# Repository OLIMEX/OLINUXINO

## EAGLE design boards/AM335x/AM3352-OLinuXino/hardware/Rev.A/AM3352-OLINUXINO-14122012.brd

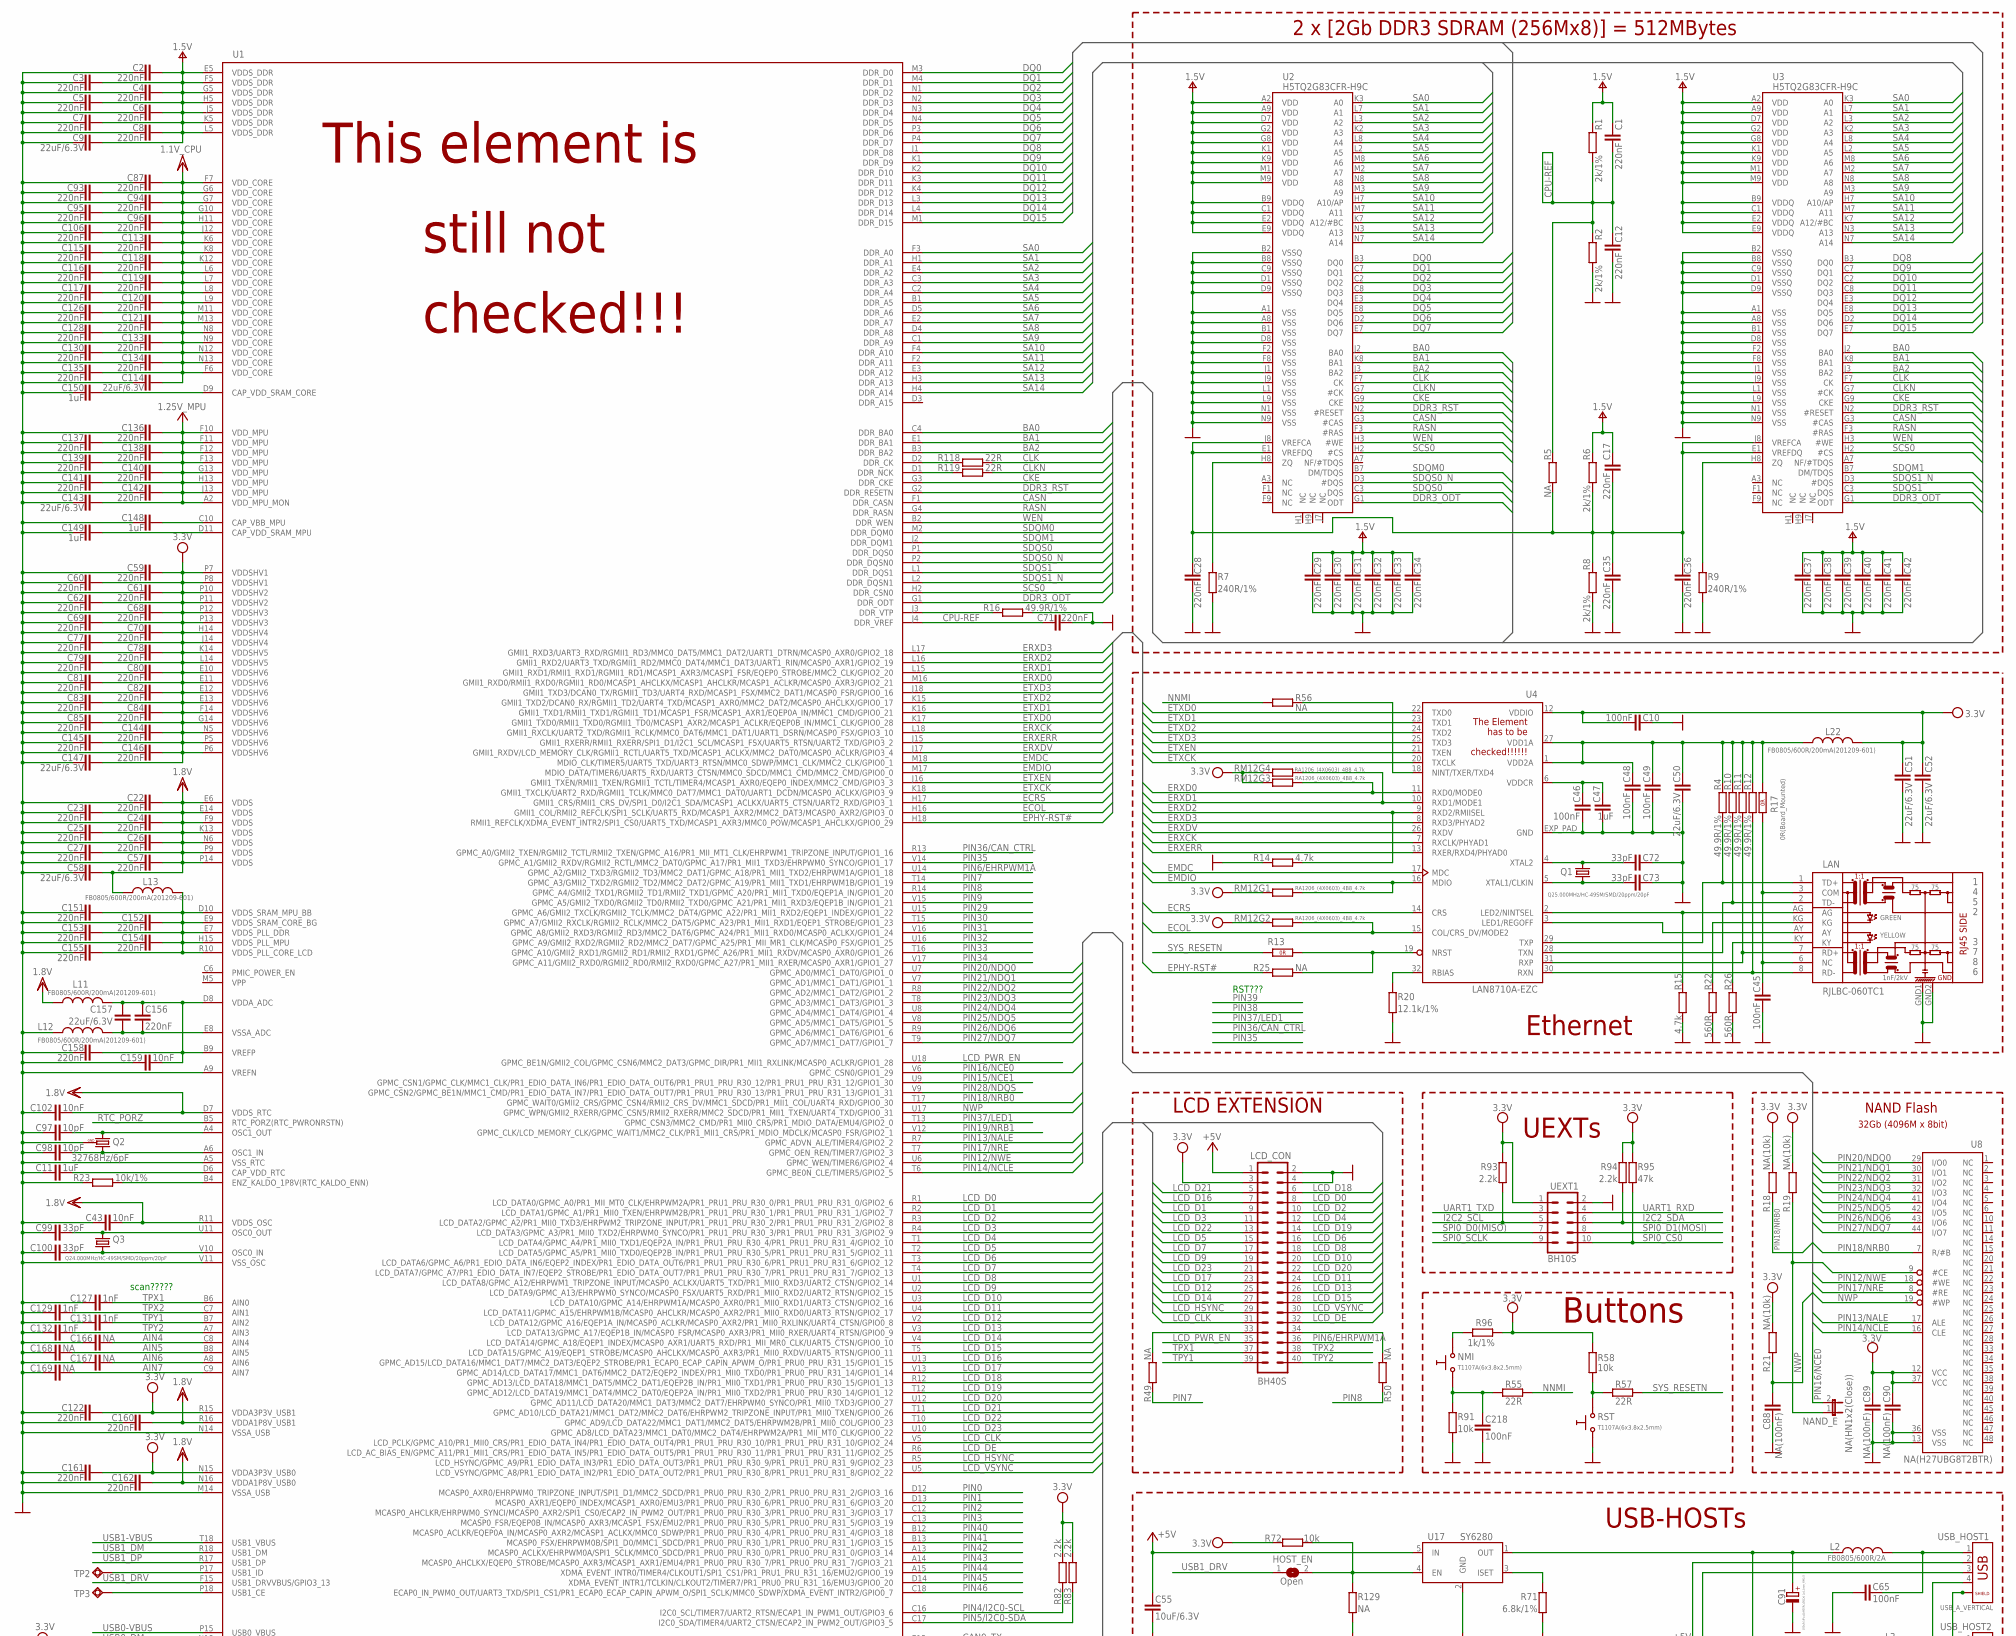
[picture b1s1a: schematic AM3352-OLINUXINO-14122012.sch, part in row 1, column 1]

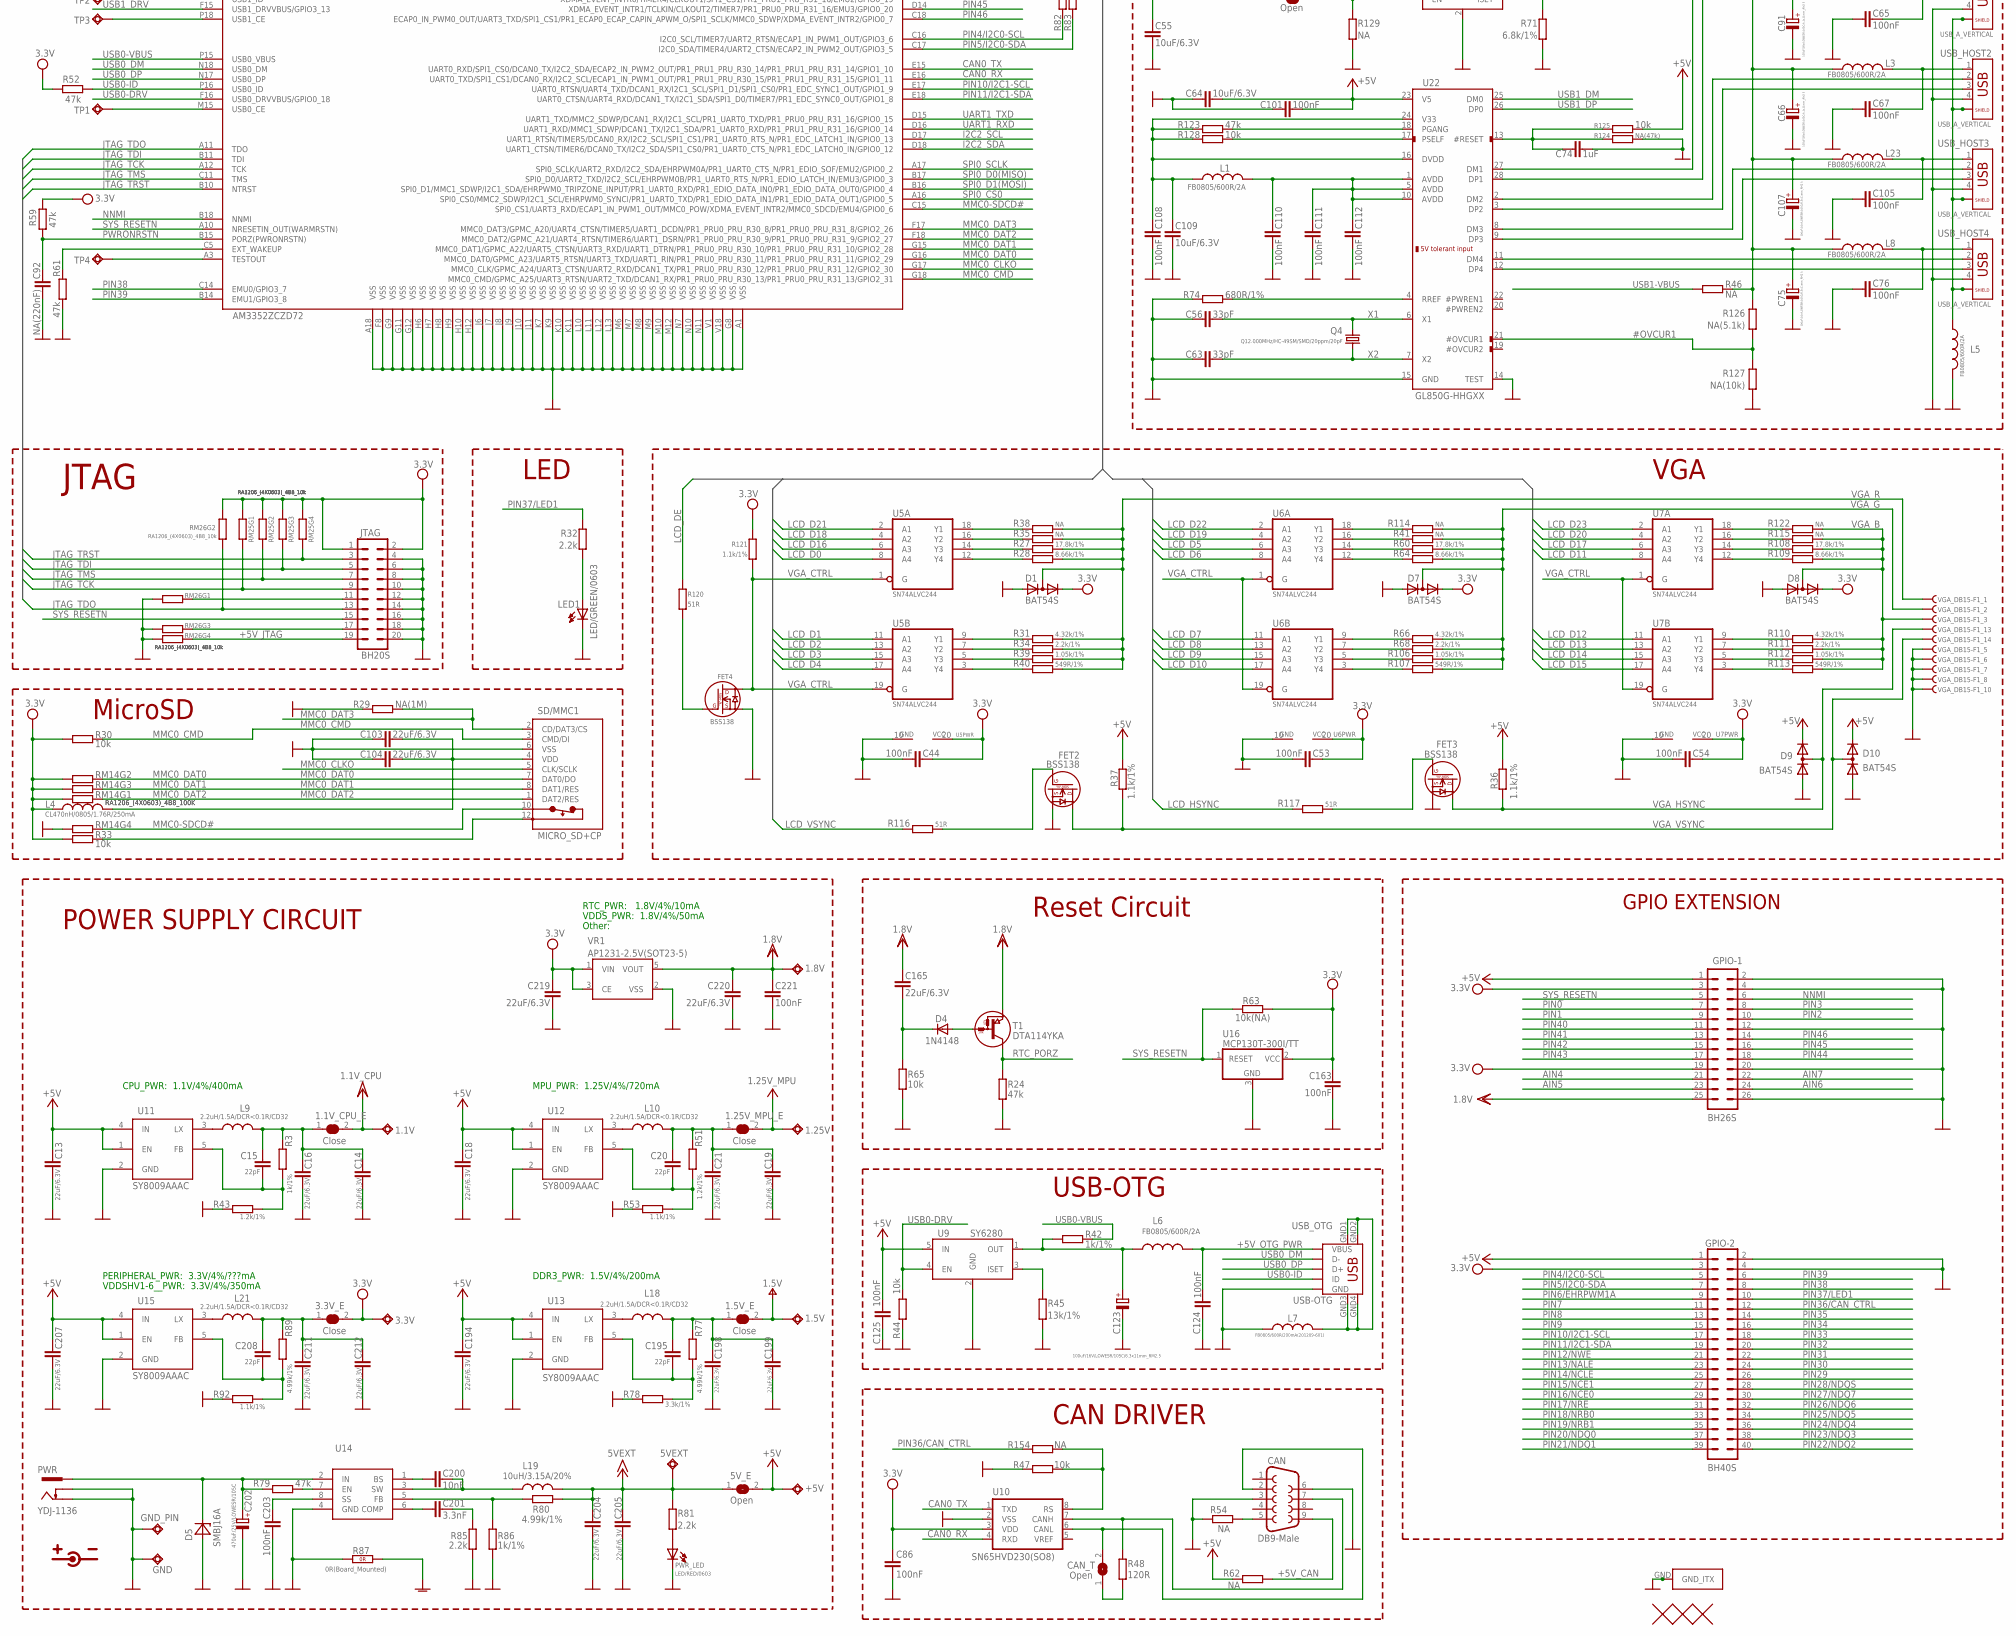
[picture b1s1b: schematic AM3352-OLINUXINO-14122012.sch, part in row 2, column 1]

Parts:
1.1V, 1.5V, 1.8V, 1.25V, 3.3V, 5VEXT: TESTPADTESTPAD_40-ROUND; TESTPAD_40-ROUND
1.1V_CPU_E, 1.5V_E, 1.25V_MPU_E, 3.3V_E: Close; SJ_1_SMALLER_CLOSE
5V_E: Open; SJ_1_SMALLER
+5V: TESTPADTESTPAD_40-ROUND; TESTPAD_40-ROUND
C1, C2, C3, C4, C5, C6, C7, C8, C12, C17, C22, C23, C24, C25, C26, C27, C28, C29, C30, C31, C32, C33, C34, C35, C36, C37, C38, C39, C40, C41, C42, C57, C59, C60, C61, C62, C68, C69, C70, C71, C77, C78, C79, C80, C81, C82, C83, C84, C85, C87, C93, C94, C95, C96, C106, C113, C115, C116, C117, C118, C119, C120, C121, C122, C126, C128, C130, C133, C134, C135, C136, C137, C138, C139, C140, C141, C142, C144, C145, C146, C151, C152, C153, C154, C155, C156, C158, C160, C161, C162: 220nF; C0603_DWS
C9, C13, C14, C16, C18, C19, C21, C50, C51, C52, C58, C103, C104, C114, C143, C147, C157, C165, C194, C198, C199, C204, C205, C207, C211, C212, C219, C220: 22uF/6.3V; C0603_DWS
C10, C44, C45, C46, C48, C49, C53, C54, C65, C67, C76, C86, C101, C105, C108, C110, C111, C112, C124, C125, C163, C203, C218, C221: 100nF; C0603_DWS
C11, C47, C74, C148, C149, C150: 1uF; C0603_DWS
C15, C20, C195, C208: 22pF; C0603_DWS
C43, C102, C159, C200: 10nF; C0603_DWS
C55, C64, C109: 10uF/6.3V; C0603_DWS
C56, C63, C72, C73, C99, C100: 33pF; C0603_DWS
C66, C75, C91, C107, C123: 100uF/16V/LOWESR/105C/6.3x11mm_RM2.5; E2,5-6,3
C88, C89, C90: NA(100nF); C0603_DWS
C92: NA(220nF); C0603_DWS
C97, C98: 10pF; C0603_DWS
C127, C129, C131, C132: 1nF; C0603_DWS
C166, C167, C168, C169: NA; C0603_DWS
C201: 3.3nF; C0603_DWS
C202: 470uF/25V/LOWESR/105C; E5-10,5
CAN: DB9-Male; F09HP-MALE
CAN_T: Open; SJ
D1, D7, D8, D9, D10: BAT54S; SOT23C(BAT54S)
D4: 1N4148; MELF-MLL41
D5: SMBJ16A; DO214AA
FET2, FET3, FET4: BSS138; SOT23
GND: TESTPADTESTPAD_40-ROUND; TESTPAD_40-ROUND
GND_PIN: TESTPAD3; TEST_PAD40/70/SQUARE
GPIO-1: BH26S; ML26
GPIO-2: BH40S; ML40
HOST_EN: Open; SJ_1_SMALLER
JTAG: BH20S; ML20-MALE
L1, L2, L3, L5, L6, L8, L23: FB0805/600R/2A; L0805_5MIL_DWS
L4: CL470nH/0805/1.76R/250mA; L0805_5MIL_DWS
L7, L11, L12, L13, L22: FB0805/600R/200mA(201209-601); L0805_5MIL_DWS
L9, L10, L18, L21: 2.2uH/1.5A/DCR<0.1R/CD32; CD32
L19: 10uH/3.15A/20%; 8X8MM_3131
LAN: RJLBC-060TC1
LCD_CON: BH40S; ML40
LED1: LED/GREEN/0603; LED-0603
NAND_E: NA(HN1x2(Close)); JP1
NMI: T1107A(6x3.8x2.5mm); SW-TAKT_6X3.5_SMD
PWR: YDJ-1136; PWR_JACK_UNI_MILLING
PWR_LED: LED/RED/0603; LED-0603
Q1: Q25.000MHz/HC-49SM/SMD/20ppm/20pF; HC49/SMD2_THIN
Q2: 32768Hz/6pF; TC26H_3_REPAIR_SMD
Q3: Q24.000MHz/HC-49SM/SMD/20ppm/20pF; HC49/SMD2_THIN
Q4: Q12.000MHz/HC-49SM/SMD/20ppm/20pF; HC49/SMD2_THIN
R1, R2, R6, R8: 2k/1%; R0603_5MIL_DWS
R3, R42, R86, R96: 1k/1%; R0603_5MIL_DWS
R4, R10, R11, R12, R16: 49.9R/1%; R0603_5MIL_DWS
R5, R25, R35, R38, R41, R46, R49, R50, R56, R114, R115, R122, R129: NA; R0603_5MIL_DWS
R7, R9: 240R/1%; R0603_5MIL_DWS
R13: R_0R0R(NA); 0603_0R
R14, R15: 4.7k; R0603_5MIL_DWS
R17, R87: 0R(Board_Mounted); 0603_0R
R18, R19, R21, R127: NA(10k); R0603_5MIL_DWS
R20: 12.1k/1%; R0603_5MIL_DWS
R22, R26: 560R; R0603_5MIL_DWS
R23: 10k/1%; R0603_5MIL_DWS
R24, R52, R59, R61, R79, R95, R123: 47k; R0603_5MIL_DWS
R27, R60, R108: 17.8k/1%; R0603_5MIL_DWS
R28, R64, R109: 8.66k/1%; R0603_5MIL_DWS
R29: NA(1M); R0603_5MIL_DWS
R30, R33, R44, R47, R58, R65, R72, R91, R125, R128: 10k; R0603_5MIL_DWS
R31, R66, R110: 4.32k/1%; R0603_5MIL_DWS
R32, R81, R82, R83, R85, R93, R94: 2.2k; R0603_5MIL_DWS
R34, R68, R111: 2.2k/1%; R0603_5MIL_DWS
R36, R37, R53, R92, R121: 1.1k/1%; R0603_5MIL_DWS
R39, R106, R112: 1.05k/1%; R0603_5MIL_DWS
R40, R107, R113: 549R/1%; R0603_5MIL_DWS
R43, R51: 1.2k/1%; R0603_5MIL_DWS
R45: 13k/1%; R0603_5MIL_DWS
R48: 120R; R1206_5MIL_WS
R54, R62, R154: NA; R0603_5MIL_DWS_NA
R55, R57, R118, R119: 22R; R0603_5MIL_DWS
R63: 10k(NA); R0603_5MIL_DWS
R71: 6.8k/1%; R0603_5MIL_DWS
R74: 680R/1%; R0603_5MIL_DWS
R77, R80, R89: 4.99k/1%; R0603_5MIL_DWS
R78: 3.3k/1%; R0603_5MIL_DWS
R116, R117, R120: 51R; R0603_5MIL_DWS
R124: NA(47k); R0603_5MIL_DWS
R126: NA(5.1k); R0603_5MIL_DWS
RM12: RA1206_(4X0603)_4B8_4.7k; R_MATRIX_4
RM14: RA1206_(4X0603)_4B8_100K; R_MATRIX_4
RM25, RM26: RA1206_(4X0603)_4B8_10k; R_MATRIX_4
RST: T1107A(6x3.8x2.5mm); SW-TAKT_6X3.5_SMD
SD/MMC1: MICRO_SD+CP; TFR-MEM-CON
T1: DTA114YKA; SOT-23
TP1, TP2, TP3, TP4: TESTPADTESTPAD_40-ROUND; TESTPAD_40-ROUND
U1: AM3352ZCZD72; S-PBGA-N324
U2, U3: H5TQ2G83CFR-H9C; FBGA78
U4: LAN8710A-EZC; QFN-32
U5, U6, U7: SN74ALVC244; PW
U8: NA(H27UBG8T2BTR); TSOP48
U9, U17: SY6280; SOT23-5
U10: SN65HVD230(SO8); SO-08
U11, U12, U13, U15: SY8009AAAC; SOT23-5
U14: MP1482DS; SOIC8
U16: MCP130T-300I/TT; SOT23
U19, U20, U21: FIDUCIAL1X2; FIDUCIAL-1X2
U22: GL850G-HHGXX; SSOP28
U$1: NANO_ITX_; NANO-ITX_140X140
UEXT1: BH10S; ML10-MALE
USB_HOST1, USB_HOST2, USB_HOST3, USB_HOST4: USB_A_VERTICAL; USB_A_VERTICAL_PTH
USB_OTG: USB-OTG; USB_MINI_9PIN
VGA_DB15-F1: VGA15; DB15-F_22MM
VR1: AP1231-2.5V(SOT23-5); SOT-23-5

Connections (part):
#OVCUR1: R126.1, R127.2, U22.21 (#OVCUR1)
+5V: 5V_E.2, +5V.1, C13.1, C18.1, C55.1, C64.1, C101.1, C125.1, C194.1, C207.1, D9.2 (K), D10.2 (K), GPIO-1.1, GPIO-2.1, LCD_CON.1, R36.2, R37.2, R62.1, R125.2, U9.5 (IN), U11.1 (EN), U11.4 (IN), U12.1 (EN), U12.4 (IN), U13.1 (EN), U13.4 (IN), U15.1 (EN), U15.4 (IN), U17.5 (IN), U22.23 (V5)
+5V_CAN: CAN.9, R62.2
+5V_JTAG: JTAG.19, RM26.4.2 (2)
+5V_OTG_PWR: C124.1, L6.1, USB_OTG.VBUS
+15V: 5VEXT.1, 5V_E.1, C204.1, C205.1, L19.2, R80.2, R81.1
AIN4: C166.2, GPIO-1.21, U1.C8 (AIN4)
AIN5: C168.2, GPIO-1.23, U1.B8 (AIN5)
AIN6: C167.2, GPIO-1.24, U1.A8 (AIN6)
AIN7: C169.2, GPIO-1.22, U1.C9 (AIN7)
AVDD1: C110.1, C111.1, C112.1, L1.2, U22.1 (AVDD), U22.5 (AVDD), U22.10 (AVDD)
BA0: U1.C4 (DDR_BA0), U2.J2 (BA0), U3.J2 (BA0)
BA1: U1.E1 (DDR_BA1), U2.K8 (BA1), U3.K8 (BA1)
BA2: U1.B3 (DDR_BA2), U2.J3 (BA2), U3.J3 (BA2)
CAN0_RX: U1.E16 (UART0_TXD/SPI1_CS1/DCAN0_RX/I2C2_SCL/EC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), U10.4 (RXD)
CAN0_TX: U1.E15 (UART0_RXD/SPI1_CS0/DCAN0_TX/I2C2_SDA/EC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), U10.1 (TXD)
CANH: CAN.7, R48.2, U10.7 (CANH)
CANL: CAN.2, CAN_T.2, U10.6 (CANL)
CASN: U1.F1 (DDR_CASN), U2.G3 (#CAS), U3.G3 (#CAS)
CKE: U1.G3 (DDR_CKE), U2.G9 (CKE), U3.G9 (CKE)
CLK: R118.1, U2.F7 (CK), U3.F7 (CK)
CLKN: R119.1, U2.G7 (#CK), U3.G7 (#CK)
CPU-REF: C1.2, C12.2, C71.2, R1.1, R2.2, R5.2, U1.J4 (DDR_VREF)
DDR3_ODT: U1.G1 (DDR_ODT), U2.G1 (ODT), U3.G1 (ODT)
DDR3_RST: U1.G2 (DDR_RESETN), U2.N2 (#RESET), U3.N2 (#RESET)
DM1: U22.27 (DM1), USB_HOST1.2
DM2: U22.2 (DM2), USB_HOST2.2
DM3: U22.8 (DM3), USB_HOST3.2
DM4: U22.11 (DM4), USB_HOST4.2
DP1: U22.28 (DP1), USB_HOST1.3
DP2: U22.3 (DP2), USB_HOST2.3
DP3: U22.9 (DP3), USB_HOST3.3
DP4: U22.12 (DP4), USB_HOST4.3
DQ0: U1.M3 (DDR_D0), U2.B3 (DQ0)
DQ1: U1.M4 (DDR_D1), U2.C7 (DQ1)
DQ2: U1.N1 (DDR_D2), U2.C2 (DQ2)
DQ3: U1.N2 (DDR_D3), U2.C8 (DQ3)
DQ4: U1.N3 (DDR_D4), U2.E3 (DQ4)
DQ5: U1.N4 (DDR_D5), U2.E8 (DQ5)
DQ6: U1.P3 (DDR_D6), U2.D2 (DQ6)
DQ7: U1.P4 (DDR_D7), U2.E7 (DQ7)
DQ8: U1.J1 (DDR_D8), U3.B3 (DQ0)
DQ9: U1.K1 (DDR_D9), U3.C7 (DQ1)
DQ10: U1.K2 (DDR_D10), U3.C2 (DQ2)
DQ11: U1.K3 (DDR_D11), U3.C8 (DQ3)
DQ12: U1.K4 (DDR_D12), U3.E3 (DQ4)
DQ13: U1.L3 (DDR_D13), U3.E8 (DQ5)
DQ14: U1.L4 (DDR_D14), U3.D2 (DQ6)
DQ15: U1.M1 (DDR_D15), U3.E7 (DQ7)
DRAM-REF: C17.2, C28.2, C35.2, C36.2, R5.1, R6.1, R8.2, U2.E1 (VREFDQ), U2.J8 (VREFCA), U3.E1 (VREFDQ), U3.J8 (VREFCA)
DVDD1: C108.1, C109.1, L1.1, R123.1, R128.1, U22.16 (DVDD), U22.24 (V33)
ECOL: RM12.2.2 (2), U1.H16 (GMII1_COL/RMII2_REFCLK/SPI1_SCLK/UART5_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), U4.15 (COL/CRS_DV/MODE2)
ECRS: U1.H17 (GMII1_CRS/RMII1_CRS_DV/SPI1_D0/I2C1_SDA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), U4.14 (CRS)
EMDC: U1.M18 (MDIO_CLK/TIMER5/UART5_TXD/UART3_RTSN/MM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), U4.17 (MDC)
EMDIO: RM12.1.2 (2), U1.M17 (MDIO_DATA/TIMER6/UART5_RXD/UART3_CTSN/M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), U4.16 (MDIO)
EPHY-RST#: R25.1, U1.H18 (RMII1_REFCLK/XDMA_EVENT_INTR2/SPI1_CS0/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)
ERXCK: U1.L18 (GMII1_RXCLK/UART2_TXD/RGMII1_RCLK/MMC0_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), U4.7 (RXCLK/PHYAD1)
ERXD0: RM12.3.2 (2), U1.M16 (GMII1_RXD0/RMII1_RXD0/RGMII1_RD0/MCASP1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), U4.11 (RXD0/MODE0)
ERXD1: RM12.4.2 (2), U1.L15 (GMII1_RXD1/RMII1_RXD1/RGMII1_RD1/MCASP1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), U4.10 (RXD1/MODE1)
ERXD2: R14.2, U1.L16 (GMII1_RXD2/UART3_TXD/RGMII1_RD2/MMC0_DA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), U4.9 (RXD2/RMIISEL)
ERXD3: U1.L17 (GMII1_RXD3/UART3_RXD/RGMII1_RD3/MMC0_DA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), U4.8 (RXD3/PHYAD2)
ERXDV: U1.J17 (GMII1_RXDV/LCD_MEMORY_CLK/RGMII1_RCTL/U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), U4.26 (RXDV)
ERXERR: U1.J15 (GMII1_RXERR/RMII1_RXERR/SPI1_D1/I2C1_SC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), U4.13 (RXER/RXD4/PHYAD0)
ETXCK: U1.K18 (GMII1_TXCLK/UART2_RXD/RGMII1_TCLK/MMC0_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), U4.20 (TXCLK)
ETXD0: U1.K17 (GMII1_TXD0/RMII1_TXD0/RGMII1_TD0/MCASP1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), U4.22 (TXD0)
ETXD1: U1.K16 (GMII1_TXD1/RMII1_TXD1/RGMII1_TD1/MCASP1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), U4.23 (TXD1)
ETXD2: U1.K15 (GMII1_TXD2/DCAN0_RX/RGMII1_TD2/UART4_TX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), U4.24 (TXD2)
ETXD3: U1.J18 (GMII1_TXD3/DCAN0_TX/RGMII1_TD3/UART4_RX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), U4.25 (TXD3)
ETXEN: U1.J16 (GMII1_TXEN/RMII1_TXEN/RGMII1_TCTL/TIMER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), U4.21 (TXEN)
GND: C2.1, C3.1, C4.1, C5.1, C6.1, C7.1, C8.1, C9.1, C10.1, C11.1, C12.1, C13.2, C14.2, C16.2, C18.2, C19.2, C21.2, C22.1, C23.1, C24.1, C25.1, C26.1, C27.1, C28.1, C29.1, C30.1, C31.1, C32.1, C33.1, C34.1, C35.1, C36.1, C37.1, C38.1, C39.1, C40.1, C41.1, C42.1, C43.1, C44.2, C45.1, C46.1, C47.1, C48.1, C49.1, C50.1, C51.1, C52.1, C53.2, C54.2, C55.2, C56.1, C57.1, C58.1, C59.1, C60.1, C61.1, C62.1, C63.1, C64.2, C65.2, C66.-, C67.2, C68.1, C69.1, C70.1, C71.1, C72.1, C73.1, C74.1, C75.-, C76.2, C77.1, C78.1, C79.1, C80.1, C81.1, C82.1, C83.1, C84.1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
GNDA: R87.2 (1.2)
I2C2_SCL: R93.1, U1.D17 (UART1_RTSN/TIMER5/DCAN0_RX/I2C2_SCL/SPI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), UEXT1.5
I2C2_SDA: R94.1, U1.D18 (UART1_CTSN/TIMER6/DCAN0_TX/I2C2_SDA/SPI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), UEXT1.6
JTAG_TCK: JTAG.9, RM25.1.1 (1), U1.A12 (TCK)
JTAG_TDI: JTAG.5, RM25.3.1 (1), U1.B11 (TDI)
JTAG_TDO: JTAG.13, RM26.2.2 (2), U1.A11 (TDO)
JTAG_TMS: JTAG.7, RM25.2.1 (1), U1.C11 (TMS)
JTAG_TRST: JTAG.3, RM25.4.1 (1), U1.B10 (NTRST)
LCD_CLK: LCD_CON.31, U1.V5 (LCD_PCLK/GPMC_A10/PR1_MII0_CRS/PR1_EDIO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)
LCD_D0: LCD_CON.8, U1.R1 (LCD_DATA0/GPMC_A0/PR1_MII_MT0_CLK/EHRPW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), U5.8 (A4)
LCD_D1: LCD_CON.9, U1.R2 (LCD_DATA1/GPMC_A1/PR1_MII0_TXEN/EHRPWM2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), U5.11 (A1)
LCD_D2: LCD_CON.10, U1.R3 (LCD_DATA2/GPMC_A2/PR1_MII0_TXD3/EHRPWM2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), U5.13 (A2)
LCD_D3: LCD_CON.11, U1.R4 (LCD_DATA3/GPMC_A3/PR1_MII0_TXD2/EHRPWM0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), U5.15 (A3)
LCD_D4: LCD_CON.12, U1.T1 (LCD_DATA4/GPMC_A4/PR1_MII0_TXD1/EQEP2A_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), U5.17 (A4)
LCD_D5: LCD_CON.15, U1.T2 (LCD_DATA5/GPMC_A5/PR1_MII0_TXD0/EQEP2B_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), U6.6 (A3)
LCD_D6: LCD_CON.16, U1.T3 (LCD_DATA6/GPMC_A6/PR1_EDIO_DATA_IN6/EQE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), U6.8 (A4)
LCD_D7: LCD_CON.17, U1.T4 (LCD_DATA7/GPMC_A7/PR1_EDIO_DATA_IN7/EQE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), U6.11 (A1)
LCD_D8: LCD_CON.18, U1.U1 (LCD_DATA8/GPMC_A12/EHRPWM1_TRIPZONE_INP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), U6.13 (A2)
LCD_D9: LCD_CON.19, U1.U2 (LCD_DATA9/GPMC_A13/EHRPWM0_SYNCO/MCASP0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), U6.15 (A3)
LCD_D10: LCD_CON.20, U1.U3 (LCD_DATA10/GPMC_A14/EHRPWM1A/MCASP0_AXR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), U6.17 (A4)
LCD_D11: LCD_CON.24, U1.U4 (LCD_DATA11/GPMC_A15/EHRPWM1B/MCASP0_AHC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), U7.8 (A4)
LCD_D12: LCD_CON.25, U1.V2 (LCD_DATA12/GPMC_A16/EQEP1A_IN/MCASP0_AC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), U7.11 (A1)
LCD_D13: LCD_CON.26, U1.V3 (LCD_DATA13/GPMC_A17/EQEP1B_IN/MCASP0_FS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), U7.13 (A2)
LCD_D14: LCD_CON.27, U1.V4 (LCD_DATA14/GPMC_A18/EQEP1_INDEX/MCASP0_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), U7.15 (A3)
LCD_D15: LCD_CON.28, U1.T5 (LCD_DATA15/GPMC_A19/EQEP1_STROBE/MCASP0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), U7.17 (A4)
LCD_D16: LCD_CON.7, U1.U13 (GPMC_AD15/LCD_DATA16/MMC1_DAT7/MMC2_DAT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), U5.6 (A3)
LCD_D17: LCD_CON.23, U1.V13 (GPMC_AD14/LCD_DATA17/MMC1_DAT6/MMC2_DAT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), U7.6 (A3)
LCD_D18: LCD_CON.6, U1.R12 (GPMC_AD13/LCD_DATA18/MMC1_DAT5/MMC2_DAT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), U5.4 (A2)
LCD_D19: LCD_CON.14, U1.T12 (GPMC_AD12/LCD_DATA19/MMC1_DAT4/MMC2_DAT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), U6.4 (A2)
LCD_D20: LCD_CON.22, U1.U12 (GPMC_AD11/LCD_DATA20/MMC1_DAT3/MMC2_DAT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), U7.4 (A2)
LCD_D21: LCD_CON.5, U1.T11 (GPMC_AD10/LCD_DATA21/MMC1_DAT2/MMC2_DAT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), U5.2 (A1)
LCD_D22: LCD_CON.13, U1.T10 (GPMC_AD9/LCD_DATA22/MMC1_DAT1/MMC2_DAT5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), U6.2 (A1)
LCD_D23: LCD_CON.21, U1.U10 (GPMC_AD8/LCD_DATA23/MMC1_DAT0/MMC2_DAT4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), U7.2 (A1)
LCD_DE: LCD_CON.32, R120.1, U1.R6 (LCD_AC_BIAS_EN/GPMC_A11/PR1_MII1_CRS/PR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)
LCD_HSYNC: LCD_CON.29, R117.1, U1.R5 (LCD_HSYNC/GPMC_A9/PR1_EDIO_DATA_IN3/PR1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)
LCD_PWR_EN: LCD_CON.35, U1.U18 (GPMC_BE1N/GMII2_COL/GPMC_CSN6/MMC2_DAT3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)
LCD_VSYNC: LCD_CON.30, R116.1, U1.U5 (LCD_VSYNC/GPMC_A8/PR1_EDIO_DATA_IN2/PR1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)
MMC0-SDCD#: RM14.4.2 (2), SD/MMC1.10 (CP_E), U1.C15 (SPI0_CS1/UART3_RXD/ECAP1_IN_PWM1_OUT/MM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)
MMC0_CLKO: SD/MMC1.5 (CLK/SCLK), U1.G17 (MMC0_CLK/GPMC_A24/UART3_CTSN/UART2_RXD/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)
MMC0_CMD: R30.1, SD/MMC1.3 (CMD/DI), U1.G18 (MMC0_CMD/GPMC_A25/UART3_RTSN/UART2_TXD/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)
MMC0_DAT0: RM14.2.1 (1), SD/MMC1.7 (DAT0/DO), U1.G16 (MMC0_DAT0/GPMC_A23/UART5_RTSN/UART3_TXD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)
MMC0_DAT1: RM14.3.1 (1), SD/MMC1.8 (DAT1/RES), U1.G15 (MMC0_DAT1/GPMC_A22/UART5_CTSN/UART3_RXD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)
MMC0_DAT2: RM14.1.1 (1), SD/MMC1.1 (DAT2/RES), U1.F18 (MMC0_DAT2/GPMC_A21/UART4_RTSN/TIMER6/UA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)
MMC0_DAT3: R29.1, SD/MMC1.2 (CD/DAT3/CS), U1.F17 (MMC0_DAT3/GPMC_A20/UART4_CTSN/TIMER5/UA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)
unnamed: C148.2, U1.C10 (CAP_VBB_MPU)
unnamed: R16.2, U1.J3 (DDR_VTP)
unnamed: R7.2, U2.H8 (ZQ)
unnamed: L9.1, U11.3 (LX)
unnamed: R9.2, U3.H8 (ZQ)
unnamed: R20.2, U4.32 (RBIAS)
unnamed: C11.2, U1.D6 (CAP_VDD_RTC)
unnamed: L18.1, U13.3 (LX)
unnamed: 1.1V_CPU_E.1, C14.1, C15.1, C16.1, L9.2, R3.1
unnamed: LAN.AG, R15.1, U4.2 (LED2/NINTSEL)
unnamed: C15.2, R3.2, R43.1, U11.5 (FB)
unnamed: R23.1, U1.B4 (ENZ_KALDO_1P8V(RTC_KALDO_ENN))
unnamed: L10.1, U12.3 (LX)
unnamed: C46.2, C47.2, U4.6 (VDDCR)
unnamed: TP1.1, U1.M15 (USB0_CE)
unnamed: 1.25V_MPU_E.1, C19.1, C20.1, C21.1, L10.2, R51.1
unnamed: C48.2, C49.2, C50.2, L22.1, R4.2, R10.2, R11.2, R12.2, R17.2 (1.2), U4.1 (VDD2A), U4.27 (VDD1A)
unnamed: 1.5V_E.1, C195.1, C198.1, C199.1, L18.2, R77.1
unnamed: C195.2, R77.2, R78.1, U13.5 (FB)
unnamed: R112.1, U7.5 (Y3)
unnamed: R110.1, U7.9 (Y1)
unnamed: C20.2, R51.2, R53.1, U12.5 (FB)
unnamed: C149.2, U1.D11 (CAP_VDD_SRAM_MPU)
unnamed: R108.1, U7.14 (Y3)
unnamed: C150.2, U1.D9 (CAP_VDD_SRAM_CORE)
unnamed: C156.1, C157.1, L12.2, U1.E8 (VSSA_ADC)
unnamed: FET2.1 (G), R116.2
unnamed: C156.2, C157.2, C158.2, C159.2, L11.2, U1.B9 (VREFP), U1.D8 (VDDA_ADC)
unnamed: FET3.1 (G), R117.2
unnamed: FET4.1 (G), R120.2
unnamed: C202.+, D5.C, PWR.+, R79.1, U14.2 (IN)
unnamed: R13.2 (1.2), R25.2, U4.19 (NRST)
unnamed: R35.1, U5.16 (Y2)
unnamed: C151.2, C152.2, C153.2, C154.2, C155.2, L13.2, U1.D10 (VDDS_SRAM_MPU_BB), U1.E7 (VDDS_PLL_DDR), U1.E9 (VDDS_SRAM_CORE_BG), U1.H15 (VDDS_PLL_MPU), U1.R10 (VDDS_PLL_CORE_LCD)
unnamed: TP2.1, U1.P17 (USB1_ID)
unnamed: C203.1, U14.8 (SS)
unnamed: R79.2, U14.7 (EN)
unnamed: TP3.1, U1.P18 (USB1_CE)
unnamed: LAN.1 (TD+), R4.1, U4.29 (TXP)
unnamed: LAN.2 (TD-), R10.1, U4.28 (TXN)
unnamed: LAN.7 (RD+), R11.1, U4.31 (RXP)
unnamed: R71.2, U17.3 (ISET)
unnamed: NMI.P$2 (1), R96.1
unnamed: C218.1, NMI.P$1 (0), R55.2, R91.1
unnamed: LAN.8 (RD-), R12.1, U4.30 (RXN)
unnamed: C200.1, U14.1 (BS)
unnamed: R38.1, U5.18 (Y1)
unnamed: R56.2, U4.18 (NINT/TXER/TXD4)
unnamed: R41.1, U6.16 (Y2)
unnamed: C200.2, L19.1, U14.3 (SW)
unnamed: R114.1, U6.18 (Y1)
unnamed: R115.1, U7.16 (Y2)
unnamed: LAN.KG, R22.1
unnamed: LAN.AY, U4.3 (LED1/REGOFF)
unnamed: R122.1, U7.18 (Y1)
unnamed: C45.2, LAN.3 (COM), LAN.6 (NC), R17.1 (1.1)
unnamed: LAN.KY, R26.1
unnamed: R33.1, SD/MMC1.12 (PACK)
unnamed: R61.2, U1.C5 (EXT_WAKEUP)
unnamed: C201.1, U14.6 (COMP)
unnamed: C201.2, R85.1
unnamed: R80.1, R86.1, U14.5 (FB)
unnamed: R57.2, R58.1, RST.P$2 (1)
unnamed: L21.1, U15.3 (LX)
unnamed: 3.3V_E.1, C208.1, C211.1, C212.1, L21.2, R89.1
unnamed: C208.2, R89.2, R92.1, U15.5 (FB)
unnamed: R74.2, U22.4 (RREF)
unnamed: R123.2, U22.18 (PGANG)
unnamed: TP4.1, U1.A3 (TESTOUT)
unnamed: D4.2 (A), T1.1 (B)
unnamed: C165.2, D4.1 (C), R65.1
unnamed: L5.2, USB_HOST1.P$3 (5), USB_HOST1.P$4 (6), USB_HOST2.P$3 (5), USB_HOST2.P$4 (6), USB_HOST3.P$3 (5), USB_HOST3.P$4 (6), USB_HOST4.P$3 (5), USB_HOST4.P$4 (6)
unnamed: C65.1, L2.2, USB_HOST1.1
unnamed: R47.1, R154.1, U10.8 (RS)
unnamed: HOST_EN.2, R72.2, R129.2, U17.4 (EN)
unnamed: C76.1, L8.2, USB_HOST4.1
unnamed: C66.+, C75.+, C91.+, C107.+, L2.1, L3.1, L8.1, L23.1, R46.2, R126.2, U17.1 (OUT)
unnamed: CAN.5, R54.2
unnamed: C97.2, Q2.1, U1.A4 (OSC1_OUT)
unnamed: R45.2, U9.3 (ISET)
unnamed: C123.+, L6.2, R42.2, U9.1 (OUT)
unnamed: R113.1, U7.3 (Y4)
unnamed: R128.2, U22.17 (PSELF)
unnamed: R111.1, U7.7 (Y2)
unnamed: R109.1, U7.12 (Y4)
unnamed: C67.1, L3.2, USB_HOST2.1
unnamed: C105.1, L23.2, USB_HOST3.1
unnamed: C98.2, Q2.2, U1.A6 (OSC1_IN)
unnamed: R66.1, U6.9 (Y1)
unnamed: R68.1, U6.7 (Y2)
unnamed: C74.2, R124.1, R125.1, U22.13 (#RESET)
unnamed: PWR_LED.A, R81.2
unnamed: R106.1, U6.5 (Y3)
unnamed: R107.1, U6.3 (Y4)
unnamed: R60.1, U6.14 (Y3)
unnamed: R64.1, U6.12 (Y4)
unnamed: R31.1, U5.9 (Y1)
unnamed: R34.1, U5.7 (Y2)
unnamed: R39.1, U5.5 (Y3)
unnamed: R40.1, U5.3 (Y4)
unnamed: R27.1, U5.14 (Y3)
unnamed: R28.1, U5.12 (Y4)
unnamed: JTAG.11, RM26.1.2 (2)
unnamed: JTAG.17, RM26.3.2 (2)
unnamed: LCD_CON.33, R49.1
unnamed: LCD_CON.34, R50.1
unnamed: LED1.A, R32.2
unnamed: NAND_E.1, R19.2, U8.9 (#CE)
unnamed: L7.2, USB_OTG.GND1, USB_OTG.GND2, USB_OTG.GND3, USB_OTG.GND4
unnamed: CAN_T.1, R48.1
NNMI: GPIO-1.6, R55.1, R56.1, U1.B18 (NNMI)
NWP: C88.2, R21.2, U1.U17 (GPMC_WPN/GMII2_RXERR/GPMC_CSN5/RMII2_RX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), U8.19 (#WP)
PIN0: GPIO-1.7, U1.D12 (MCASP0_AXR0/EHRPWM0_TRIPZONE_INPUT/SPI1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)
PIN1: GPIO-1.9, U1.D13 (MCASP0_AXR1/EQEP0_INDEX/MCASP1_AXR0/EMU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)
PIN2: GPIO-1.10, U1.C12 (MCASP0_AHCLKR/EHRPWM0_SYNCI/MCASP0_AXR2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)
PIN3: GPIO-1.8, U1.C13 (MCASP0_FSR/EQEP0B_IN/MCASP0_AXR3/MCASP1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)
PIN4/I2C0-SCL: GPIO-2.5, R82.1, U1.C16 (I2C0_SCL/TIMER7/UART2_RTSN/ECAP1_IN_PWM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)
PIN5/I2C0-SDA: GPIO-2.7, R83.1, U1.C17 (I2C0_SDA/TIMER4/UART2_CTSN/ECAP2_IN_PWM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)
PIN6/EHRPWM1A: GPIO-2.9, LCD_CON.36, U1.U14 (GPMC_A2/GMII2_TXD3/RGMII2_TD3/MMC2_DAT1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)
PIN7: GPIO-2.11, R49.2, U1.T14 (GPMC_A3/GMII2_TXD2/RGMII2_TD2/MMC2_DAT2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)
PIN8: GPIO-2.13, R50.2, U1.R14 (GPMC_A4/GMII2_TXD1/RGMII2_TD1/RMII2_TXD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)
PIN9: GPIO-2.15, U1.V15 (GPMC_A5/GMII2_TXD0/RGMII2_TD0/RMII2_TXD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)
PIN10/I2C1-SCL: GPIO-2.17, U1.E17 (UART0_RTSN/UART4_TXD/DCAN1_RX/I2C1_SCL/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)
PIN11/I2C1-SDA: GPIO-2.19, U1.E18 (UART0_CTSN/UART4_RXD/DCAN1_TX/I2C1_SDA/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)
PIN12/NWE: GPIO-2.21, U1.U6 (GPMC_WEN/TIMER6/GPIO2_4), U8.18 (#WE)
PIN13/NALE: GPIO-2.23, U1.R7 (GPMC_ADVN_ALE/TIMER4/GPIO2_2), U8.17 (ALE)
PIN14/NCLE: GPIO-2.25, U1.T6 (GPMC_BE0N_CLE/TIMER5/GPIO2_5), U8.16 (CLE)
PIN15/NCE1: GPIO-2.27, U1.U9 (GPMC_CSN1/GPMC_CLK/MMC1_CLK/PR1_EDIO_DA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)
PIN16/NCE0: GPIO-2.29, NAND_E.2, U1.V6 (GPMC_CSN0/GPIO1_29)
PIN17/NRE: GPIO-2.31, U1.T7 (GPMC_OEN_REN/TIMER7/GPIO2_3), U8.8 (#RE)
PIN18/NRB0: GPIO-2.33, R18.2, U1.T17 (GPMC_WAIT0/GMII2_CRS/GPMC_CSN4/RMII2_CR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), U8.7 (R/#B)
PIN19/NRB1: GPIO-2.35, U1.V12 (GPMC_CLK/LCD_MEMORY_CLK/GPMC_WAIT1/MMC2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)
PIN20/NDQ0: GPIO-2.37, U1.U7 (GPMC_AD0/MMC1_DAT0/GPIO1_0), U8.29 (I/O0)
PIN21/NDQ1: GPIO-2.39, U1.V7 (GPMC_AD1/MMC1_DAT1/GPIO1_1), U8.30 (I/O1)
PIN22/NDQ2: GPIO-2.40, U1.R8 (GPMC_AD2/MMC1_DAT2/GPIO1_2), U8.31 (I/O2)
PIN23/NDQ3: GPIO-2.38, U1.T8 (GPMC_AD3/MMC1_DAT3/GPIO1_3), U8.32 (I/O3)
PIN24/NDQ4: GPIO-2.36, U1.U8 (GPMC_AD4/MMC1_DAT4/GPIO1_4), U8.41 (I/O4)
PIN25/NDQ5: GPIO-2.34, U1.V8 (GPMC_AD5/MMC1_DAT5/GPIO1_5), U8.42 (I/O5)
PIN26/NDQ6: GPIO-2.32, U1.R9 (GPMC_AD6/MMC1_DAT6/GPIO1_6), U8.43 (I/O6)
PIN27/NDQ7: GPIO-2.30, U1.T9 (GPMC_AD7/MMC1_DAT7/GPIO1_7), U8.44 (I/O7)
PIN28/NDQS: GPIO-2.28, U1.V9 (GPMC_CSN2/GPMC_BE1N/MMC1_CMD/PR1_EDIO_D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)
PIN29: GPIO-2.26, U1.U15 (GPMC_A6/GMII2_TXCLK/RGMII2_TCLK/MMC2_DA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)
PIN30: GPIO-2.24, U1.T15 (GPMC_A7/GMII2_RXCLK/RGMII2_RCLK/MMC2_DA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)
PIN31: GPIO-2.22, U1.V16 (GPMC_A8/GMII2_RXD3/RGMII2_RD3/MMC2_DAT6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)
PIN32: GPIO-2.20, U1.U16 (GPMC_A9/GMII2_RXD2/RGMII2_RD2/MMC2_DAT7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)
PIN33: GPIO-2.18, U1.T16 (GPMC_A10/GMII2_RXD1/RGMII2_RD1/RMII2_RX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)
PIN34: GPIO-2.16, U1.V17 (GPMC_A11/GMII2_RXD0/RGMII2_RD0/RMII2_RX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)
PIN35: GPIO-2.14, U1.V14 (GPMC_A1/GMII2_RXDV/RGMII2_RCTL/MMC2_DAT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)
PIN36/CAN_CTRL: GPIO-2.12, R154.2, U1.R13 (GPMC_A0/GMII2_TXEN/RGMII2_TCTL/RMII2_TX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)
PIN37/LED1: GPIO-2.10, R32.1, U1.T13 (GPMC_CSN3/MMC2_CMD/PR1_MII0_CRS/PR1_MDI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)
PIN38: GPIO-2.8, U1.C14 (EMU0/GPIO3_7)
PIN39: GPIO-2.6, U1.B14 (EMU1/GPIO3_8)
PIN40: GPIO-1.11, U1.B12 (MCASP0_ACLKR/EQEP0A_IN/MCASP0_AXR2/MCAS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)
PIN41: GPIO-1.13, U1.B13 (MCASP0_FSX/EHRPWM0B/SPI1_D0/MMC1_SDCD/P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)
PIN42: GPIO-1.15, U1.A13 (MCASP0_ACLKX/EHRPWM0A/SPI1_SCLK/MMC0_SD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)
PIN43: GPIO-1.17, U1.A14 (MCASP0_AHCLKX/EQEP0_STROBE/MCASP0_AXR3/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)
PIN44: GPIO-1.18, U1.A15 (XDMA_EVENT_INTR0/TIMER4/CLKOUT1/SPI1_CS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)
PIN45: GPIO-1.16, U1.D14 (XDMA_EVENT_INTR1/TCLKIN/CLKOUT2/TIMER7/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)
PIN46: GPIO-1.14, U1.C18 (ECAP0_IN_PWM0_OUT/UART3_TXD/SPI1_CS1/PR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)
PWRONRSTN: C92.2, R59.2, U1.B15 (PORZ(PWRONRSTN))
RASN: U1.G4 (DDR_RASN), U2.F3 (#RAS), U3.F3 (#RAS)
RTC_PORZ: R24.1, T1.3 (C), U1.B5 (RTC_PORZ(RTC_PWRONRSTN))
SA0: U1.F3 (DDR_A0), U2.K3 (A0), U3.K3 (A0)
SA1: U1.H1 (DDR_A1), U2.L7 (A1), U3.L7 (A1)
SA2: U1.E4 (DDR_A2), U2.L3 (A2), U3.L3 (A2)
SA3: U1.C3 (DDR_A3), U2.K2 (A3), U3.K2 (A3)
SA4: U1.C2 (DDR_A4), U2.L8 (A4), U3.L8 (A4)
SA5: U1.B1 (DDR_A5), U2.L2 (A5), U3.L2 (A5)
SA6: U1.D5 (DDR_A6), U2.M8 (A6), U3.M8 (A6)
SA7: U1.E2 (DDR_A7), U2.M2 (A7), U3.M2 (A7)
SA8: U1.D4 (DDR_A8), U2.N8 (A8), U3.N8 (A8)
SA9: U1.C1 (DDR_A9), U2.M3 (A9), U3.M3 (A9)
SA10: U1.F4 (DDR_A10), U2.H7 (A10/AP), U3.H7 (A10/AP)
SA11: U1.F2 (DDR_A11), U2.M7 (A11), U3.M7 (A11)
SA12: U1.E3 (DDR_A12), U2.K7 (A12/#BC), U3.K7 (A12/#BC)
SA13: U1.H3 (DDR_A13), U2.N3 (A13), U3.N3 (A13)
SA14: U1.H4 (DDR_A14), U2.N7 (A14), U3.N7 (A14)
SCK: R118.2, U1.D2 (DDR_CK)
SCK#: R119.2, U1.D1 (DDR_NCK)
SCS0: U1.H2 (DDR_CSN0), U2.H2 (#CS), U3.H2 (#CS)
SDQM0: U1.M2 (DDR_DQM0), U2.B7 (DM/TDQS)
SDQM1: U1.J2 (DDR_DQM1), U3.B7 (DM/TDQS)
SDQS0: U1.P1 (DDR_DQS0), U2.C3 (DQS)
SDQS0_N: U1.P2 (DDR_DQSN0), U2.D3 (#DQS)
SDQS1: U1.L1 (DDR_DQS1), U3.C3 (DQS)
SDQS1_N: U1.L2 (DDR_DQSN1), U3.D3 (#DQS)
SD_VCC: C103.2, C104.2, L4.2, SD/MMC1.4 (VDD)
SPI0_CS0: R95.1, U1.A16 (SPI0_CS0/MMC2_SDWP/I2C1_SCL/EHRPWM0_SYN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), UEXT1.10
SPI0_D0(MISO): U1.B17 (SPI0_D0/UART2_TXD/I2C2_SCL/EHRPWM0B/PR1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), UEXT1.7
SPI0_D1(MOSI): U1.B16 (SPI0_D1/MMC1_SDWP/I2C1_SDA/EHRPWM0_TRIP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), UEXT1.8
SPI0_SCLK: U1.A17 (SPI0_SCLK/UART2_RXD/I2C2_SDA/EHRPWM0A/P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), UEXT1.9
SYS_RESETN: GPIO-1.5, JTAG.15, R13.1 (1.1), R57.1, R63.1, U1.A10 (NRESETIN_OUT(WARMRSTN)), U16.1 (RESET)
TPX1: C127.2, LCD_CON.37, U1.B6 (AIN0)
TPX2: C129.2, LCD_CON.38, U1.C7 (AIN1)
TPY1: C131.2, LCD_CON.39, U1.B7 (AIN2)
TPY2: C132.2, LCD_CON.40, U1.A7 (AIN3)
UART1_RXD: U1.D16 (UART1_RXD/MMC1_SDWP/DCAN1_TX/I2C1_SDA/P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), UEXT1.4
UART1_TXD: U1.D15 (UART1_TXD/MMC2_SDWP/DCAN1_RX/I2C1_SCL/P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), UEXT1.3
USB0-DRV: R44.2, U1.F16 (USB0_DRVVBUS/GPIO0_18), U9.4 (EN)
USB0-ID: R52.2, U1.P16 (USB0_ID), USB_OTG.ID
USB0-VBUS: R42.1, U1.P15 (USB0_VBUS)
USB0_DM: U1.N18 (USB0_DM), USB_OTG.D-
USB0_DP: U1.N17 (USB0_DP), USB_OTG.D+
USB1-VBUS: R46.1, U1.T18 (USB1_VBUS)
USB1_DM: U1.R18 (USB1_DM), U22.25 (DM0)
USB1_DP: U1.R17 (USB1_DP), U22.26 (DP0)
USB1_DRV: HOST_EN.1, U1.F15 (USB1_DRVVBUS/GPIO3_13)
V+: 1.5V.1, 1.5V_E.2, C1.1, C2.2, C3.2, C4.2, C5.2, C6.2, C7.2, C8.2, C9.2, C17.1, C29.2, C30.2, C31.2, C32.2, C33.2, C34.2, C37.2, C38.2, C39.2, C40.2, C41.2, C42.2, R1.2, R6.2, U1.E5 (VDDS_DDR), U1.F5 (VDDS_DDR), U1.G5 (VDDS_DDR), U1.H5 (VDDS_DDR), U1.J5 (VDDS_DDR), U1.K5 (VDDS_DDR), U1.L5 (VDDS_DDR), U2.A2 (VDD), U2.A9 (VDD), U2.B9 (VDDQ), U2.C1 (VDDQ), U2.D7 (VDD), U2.E2 (VDDQ), U2.E9 (VDDQ), U2.G2 (VDD), U2.G8 (VDD), U2.K1 (VDD), U2.K9 (VDD), U2.M1 (VDD), U2.M9 (VDD), U3.A2 (VDD), U3.A9 (VDD), U3.B9 (VDDQ), U3.C1 (VDDQ), U3.D7 (VDD), U3.E2 (VDDQ), U3.E9 (VDDQ), U3.G2 (VDD), U3.G8 (VDD), U3.K1 (VDD), U3.K9 (VDD), U3.M1 (VDD), U3.M9 (VDD)
VCC: 3.3V.1, 3.3V_E.2, C10.2, C44.1, C51.2, C52.2, C53.1, C54.1, C59.2, C60.2, C61.2, C62.2, C68.2, C69.2, C70.2, C77.2, C78.2, C79.2, C80.2, C81.2, C82.2, C83.2, C84.2, C85.2, C86.1, C89.2, C90.2, C122.2, C144.2, C145.2, C146.2, C147.2, C161.2, C163.1, C219.1, D1.2 (K), D7.2 (K), D8.2 (K), GPIO-1.3, GPIO-1.19, GPIO-2.3, JTAG.1, JTAG.2, L4.1, L22.2, LCD_CON.3, R18.1, R19.1, R21.1, R30.2, R33.2, R52.1, R58.2, R59.1, R63.2, R72.1, R82.2, R83.2, R93.2, R94.2, R95.2, R96.2, R121.2, RM12.1.1 (1), RM12.2.1 (1), RM12.3.1 (1), RM12.4.1 (1), RM14.1.2 (2), RM14.2.2 (2), RM14.3.2 (2), RM25.1.2 (2), RM25.2.2 (2), RM25.3.2 (2), RM25.4.2 (2), RM26.2.1 (1), U1.E10 (VDDSHV6), U1.E11 (VDDSHV6), U1.E12 (VDDSHV6), U1.E13 (VDDSHV6), U1.F14 (VDDSHV6)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
VCC/2: 1.1V.1, 1.1V_CPU_E.2, C87.2, C93.2, C94.2, C95.2, C96.2, C106.2, C113.2, C114.2, C115.2, C116.2, C117.2, C118.2, C119.2, C120.2, C121.2, C126.2, C128.2, C130.2, C133.2, C134.2, C135.2, U1.F6 (VDD_CORE), U1.F7 (VDD_CORE), U1.G6 (VDD_CORE), U1.G7 (VDD_CORE), U1.G10 (VDD_CORE), U1.H11 (VDD_CORE), U1.J12 (VDD_CORE), U1.K6 (VDD_CORE), U1.K8 (VDD_CORE), U1.K12 (VDD_CORE), U1.L6 (VDD_CORE), U1.L7 (VDD_CORE), U1.L8 (VDD_CORE), U1.L9 (VDD_CORE), U1.M11 (VDD_CORE), U1.M13 (VDD_CORE), U1.N8 (VDD_CORE), U1.N9 (VDD_CORE), U1.N12 (VDD_CORE), U1.N13 (VDD_CORE)
VCCINT: 1.25V.1, 1.25V_MPU_E.2, C136.2, C137.2, C138.2, C139.2, C140.2, C141.2, C142.2, C143.2, U1.A2 (VDD_MPU_MON), U1.F10 (VDD_MPU), U1.F11 (VDD_MPU), U1.F12 (VDD_MPU), U1.F13 (VDD_MPU), U1.G13 (VDD_MPU), U1.H13 (VDD_MPU), U1.J13 (VDD_MPU)
VDD: 1.8V.1, C22.2, C23.2, C24.2, C25.2, C26.2, C27.2, C43.2, C57.2, C58.2, C102.2, C160.2, C162.2, C165.1, C220.1, C221.1, GPIO-1.25, L11.1, L13.1, T1.2 (E), U1.D7 (VDDS_RTC), U1.E6 (VDDS), U1.E14 (VDDS), U1.F9 (VDDS), U1.K13 (VDDS), U1.N6 (VDDS), U1.N16 (VDDA1P8V_USB0), U1.P9 (VDDS), U1.P14 (VDDS), U1.R11 (VDDS_OSC), U1.R16 (VDDA1P8V_USB1), VR1.5 (VOUT)
VGA_B: D8.3 (AK), R108.2, R109.2, R110.2, R111.2, R112.2, R113.2, R115.2, R122.2, VGA_DB15-F1.3 (F)
VGA_CTRL: FET4.3 (D), R121.1, U5.1 (G), U5.19 (G), U6.1 (G), U6.19 (G), U7.1 (G), U7.19 (G)
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
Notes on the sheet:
POWER SUPPLY CIRCUIT
2 x [2Gb DDR3 SDRAM (256Mx8)] = 512MBytes
MicroSD
UEXTs
Buttons
USB-OTG
NAND Flash
32Gb (4096M x 8bit)
GPIO EXTENSION
LCD EXTENSION
Ethernet
JTAG
LED
RST???
VGA
USB-HOSTs
CAN DRIVER
CPU_PWR: 1.1V/4%/400mA
DDR3_PWR: 1.5V/4%/200mA
PERIPHERAL_PWR: 3.3V/4%/???mA
MPU_PWR: 1.25V/4%/720mA
RTC_PWR: 1.8V/4%/10mA
VDDS_PWR: 1.8V/4%/50mA
VDDSHV1-6__PWR: 3.3V/4%/350mA
Other:
scan?????
Reset Circuit

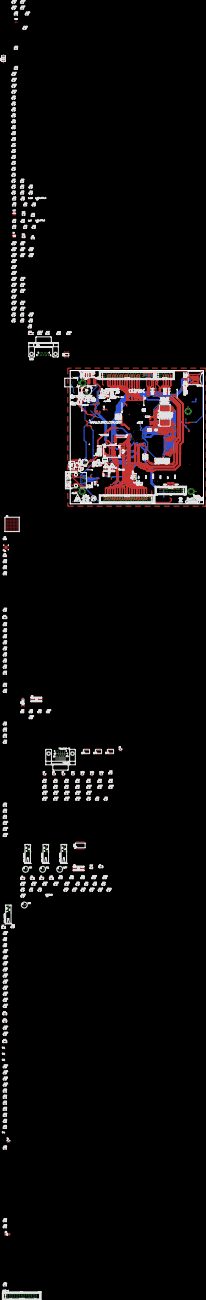
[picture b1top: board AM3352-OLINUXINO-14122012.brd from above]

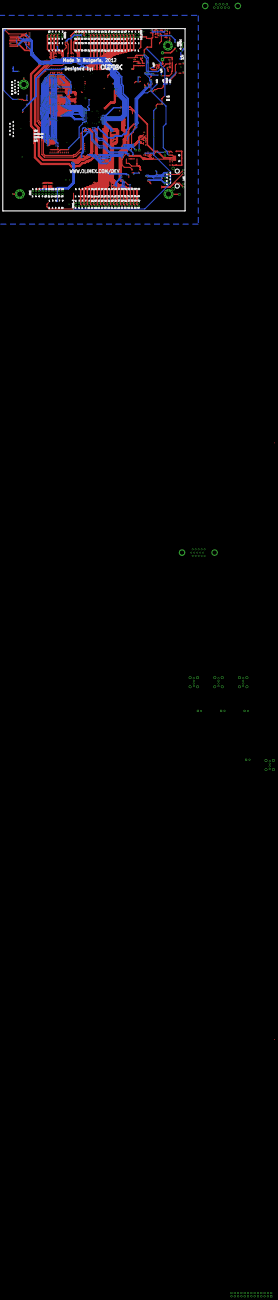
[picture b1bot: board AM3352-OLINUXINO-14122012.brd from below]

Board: 4 copper layers, 139.7 x 139.7 mm, 405 parts (7 on the bottom side), 338 nets.

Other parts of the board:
U$5: LOGO-OPENHARDWARE_8X8
U$6, U$8: OLIMEX1_V
U$9: PB
U$10: ESD_SYMBOL
U$11: RECYCLE_BIN1/8
U$12: ROHS
